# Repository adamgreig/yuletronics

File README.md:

# Yuletronics: Electronics Club Project Michaelmas 2016

This repository contains the example Yuletronics project for Electronics Club. 
You can either use git to clone it, or simply download it 
[here](https://github.com/adamgreig/yuletronics/archive/master.zip).

You'll need KiCAD to open and edit the PCB: [download it 
here](http://kicad.org/). If you can easily get a nightly build, they have 
a few nice new features.

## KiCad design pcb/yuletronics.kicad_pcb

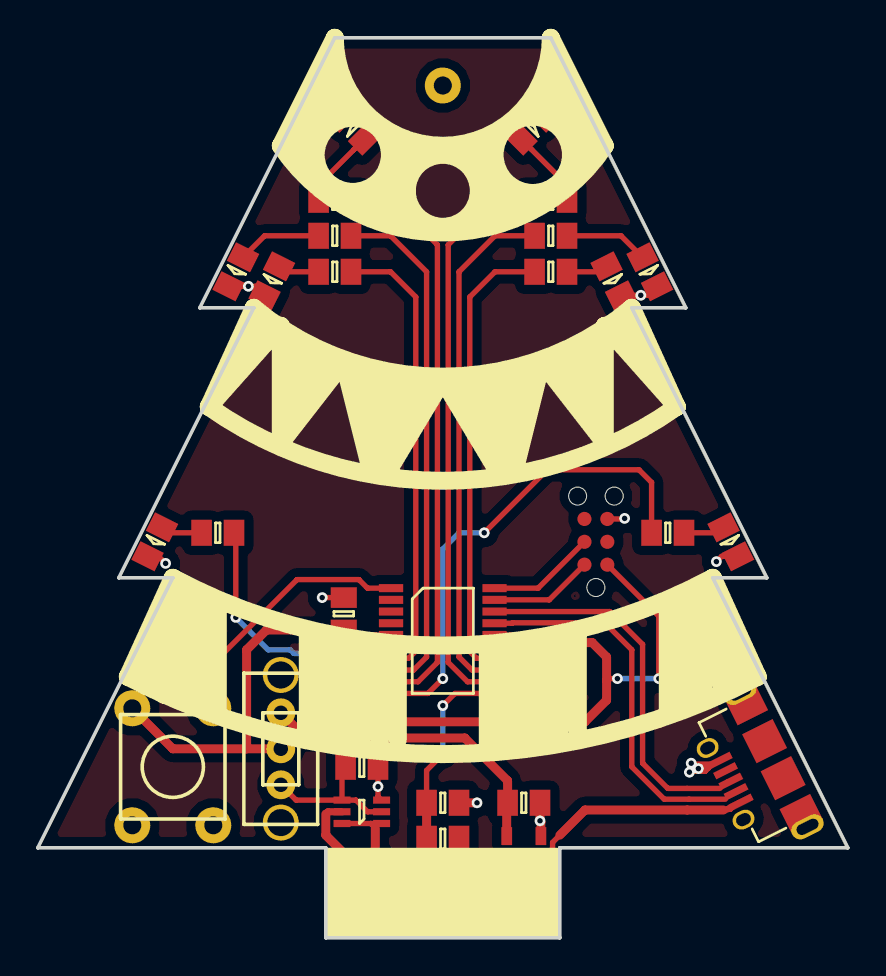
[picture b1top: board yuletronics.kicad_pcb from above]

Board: 2 copper layers, 45.0 x 50.0 mm, 35 parts (1 on the bottom side), 29 nets.

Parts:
C1, C4, C7: 10µ; 0805
C2, C3: 100n; 0805
C5, C6: 1µ; 0805
D1, D2, D3, D4, D5, D6, D7, D8: LED; 0805-LED
IC1: STM32F042F6P6; TSSOP-20
IC2: MCP1700; SOT-23
IC3: TLV61225; SC-70-6
J1: BATT; AAA_HOLDER
J2: MICROUSB; MICROUSB_MOLEX_47589-0001
L1: 4µ7; 2016M
P1: SWD_TC; TC2030-NL
R1, R2, R3: 10k; 0805
R4, R5, R6, R7, R8, R9, R10, R11: R; 0805
SW1: BOOTLOAD; MOM_SWITCH
SW2: PWR_SWITCH; SPDT_SWITCH

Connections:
3v3: C1.2, C2.2, C3.2, IC1.5, IC1.16, P1.1, SW1.1, SW2.2
5v: C5.1, IC2.3, J2.1, R2.1
/BATT_3V3: C7.1, IC3.2, IC3.4, SW2.1
/LED1: IC1.6, R4.1
/LED2: IC1.7, R5.1
/LED3: IC1.8, R6.1
/LED4: IC1.9, R7.1
/LED5: IC1.10, R8.1
/LED6: IC1.12, R9.1
/LED7: IC1.13, R10.1
/LED8: IC1.14, R11.1
/SWCLK: IC1.20, P1.4
/SWDIO: IC1.19, P1.2
/SWITCH: IC1.1, R1.1, SW1.2
/USB_3V3: C6.1, IC2.2, SW2.3
/USB_DETECT: IC1.11, R2.2, R3.1
/USB_DM: IC1.17, J2.2
/USB_DP: IC1.18, J2.3
/VBATT: C4.1, IC3.1, IC3.6, J1.2, L1.1
GND: C1.1, C2.1, C3.1, C4.2, C5.2, C6.2, C7.2, D1.1, D2.1, D3.1, D4.1, D5.1, D6.1, D7.1, D8.1, IC1.15, IC2.1, IC3.3, J1.1, J2.5, P1.5, R1.2, R3.2
unnamed: D1.2, R4.2
unnamed: D2.2, R5.2
unnamed: D3.2, R6.2
unnamed: D4.2, R7.2
unnamed: D5.2, R8.2
unnamed: D6.2, R9.2
unnamed: D7.2, R10.2
unnamed: D8.2, R11.2
unnamed: IC3.5, L1.2

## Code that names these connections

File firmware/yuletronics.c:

#include <stdint.h>
#include <stdbool.h>

#include <libopencm3/stm32/rcc.h>
#include <libopencm3/stm32/gpio.h>

#define LED1 GPIO0
#define LED2 GPIO1
#define LED3 GPIO2
#define LED4 GPIO3
#define LED5 GPIO4
#define LED6 GPIO6
#define LED7 GPIO7
#define LED8 GPIO1

#define LED1_PORT GPIOA
#define LED2_PORT GPIOA
#define LED3_PORT GPIOA
#define LED4_PORT GPIOA
#define LED5_PORT GPIOA
#define LED6_PORT GPIOA
#define LED7_PORT GPIOA
#define LED8_PORT GPIOB

static const uint16_t led_pins[] = {
    0,
    LED1, LED2, LED3, LED4, LED5, LED6, LED7, LED8
};

static const uint32_t led_ports[] = {
    0,
    LED1_PORT, LED2_PORT, LED3_PORT, LED4_PORT,
    LED5_PORT, LED6_PORT, LED7_PORT, LED8_PORT
};

#define TURNON(led) gpio_set(led_ports[led], led_pins[led])
#define TURNOFF(led) gpio_clear(led_ports[led], led_pins[led])

static void gpio_setup(void)
{
    int led;

    rcc_periph_clock_enable(RCC_GPIOA);
    rcc_periph_clock_enable(RCC_GPIOB);

    for(led=1; led<=8; led++) {
        gpio_clear(led_ports[led], led_pins[led]);
        gpio_mode_setup(
            led_ports[led], GPIO_MODE_OUTPUT, GPIO_PUPD_NONE, led_pins[led]);
        gpio_set_output_options(
            led_ports[led], GPIO_OTYPE_PP, GPIO_OSPEED_LOW, led_pins[led]);
    }
}

static void wait(void)
{
    volatile int i;
    for(i=0; i<100000; i++);
}

int main(void)
{
    gpio_setup();

    while(true)
    {
        TURNON(1);
        TURNON(5);
        wait();
        TURNON(3);
        TURNON(7);
        wait();
        TURNOFF(1);
        TURNOFF(5);
        wait();
        TURNOFF(3);
        TURNOFF(7);
        TURNON(2);
        TURNON(8);
        wait();
        TURNOFF(2);
        TURNOFF(8);
    }
    return 0;
}

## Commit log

2016-10-12 Initial commit. Layout of example PCB.
2016-10-12 Make PCB file compatibile with stable KiCAD 4.0.4
2016-10-18 Add README
2016-10-20 Type in README.md
2016-11-04 regen bom
2016-11-04 first go at firmware
2016-11-04 Added USB device ID to DFU command
2021-11-09 Update README.md
    https://forum.kicad.info/t/warning-avoid-all-links-to-kicad-pcb-org-use-kicad-org/31521
